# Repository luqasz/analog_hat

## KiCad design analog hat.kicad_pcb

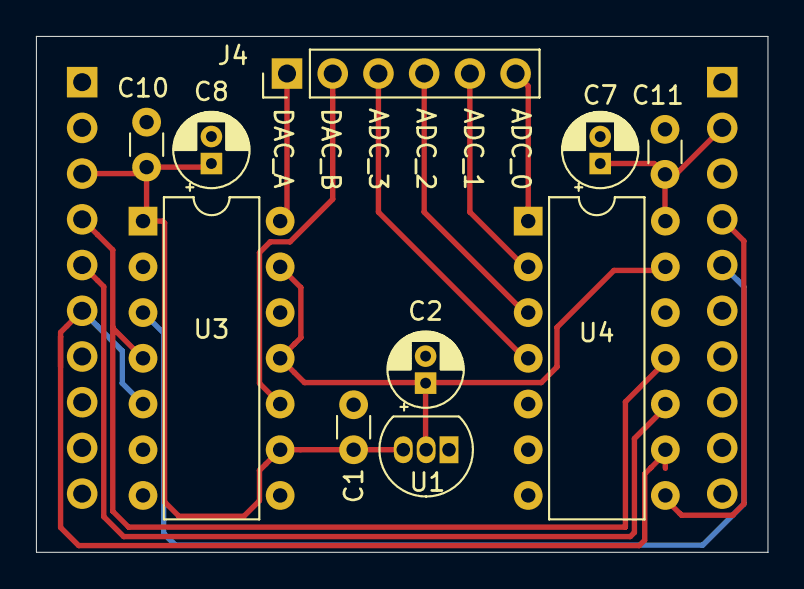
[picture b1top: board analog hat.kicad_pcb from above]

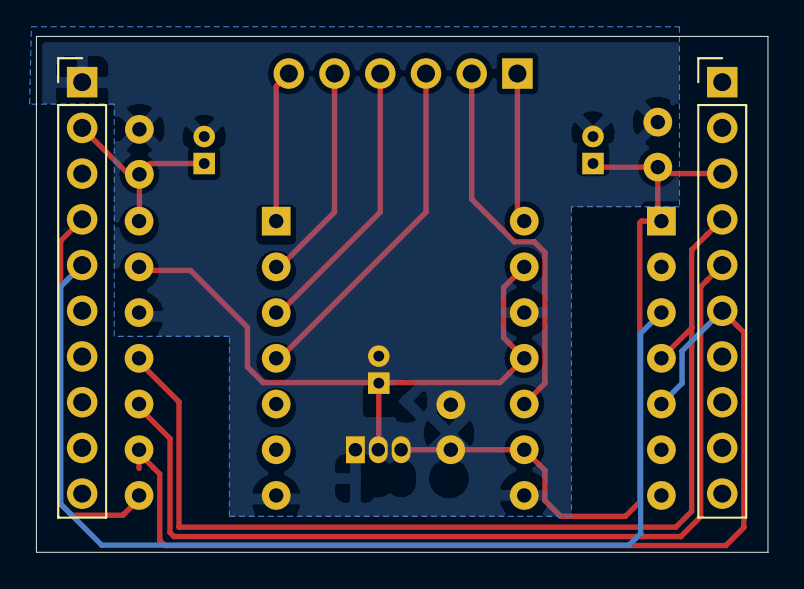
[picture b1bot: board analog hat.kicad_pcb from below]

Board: 2 copper layers, 40.6 x 28.7 mm, 12 parts (2 on the bottom side), 14 nets.

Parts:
C1, C10, C11: 100nF; C_Disc_D3.0mm_W1.6mm_P2.50mm
C2, C7, C8: 10uF; CP_Radial_D4.0mm_P1.50mm
J4: Conn_01x06; PinHeader_1x06_P2.54mm_Vertical
J5, J6: Conn_01x10; PinHeader_1x10_P2.54mm_Vertical
U1: MCP1541-TO; TO-92_Inline
U3: MCP4922-ESL; DIP-14_W7.62mm
U4: MCP3204; DIP-14_W7.62mm

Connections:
/ADC_CS: J6.4, U4.8
/DAC_CS: J6.5, U3.3
/MISO: J5.5, U4.10
/MOSI: J5.6, U3.5, U4.9
/SCK: J5.4, U3.4, U4.11
/VREF: C2.1, U1.2, U3.11, U3.13, U4.13
GNDA: C1.2, C2.2, C7.2, C8.2, C10.2, C11.2, J6.1, U1.1, U3.8, U3.12, U4.7, U4.12
unnamed: J4.1, U3.14
unnamed: J4.2, U3.10
unnamed: J4.3, U4.4
unnamed: J4.4, U4.3
unnamed: J4.5, U4.2
unnamed: J4.6, U4.1
VCC: C1.1, C7.1, C8.1, C10.1, C11.1, J5.3, J6.2, U1.3, U3.1, U3.9, U4.14

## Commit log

2019-10-16 Add license
2019-10-16 Fix ICs placement
